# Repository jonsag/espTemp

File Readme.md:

# espTemp

An ESP-01 module with a DHT22 temperature sensor  
KiCad/espTemp/espTemp.png
Modified from [https://randomnerdtutorials.com/esp8266-dht11dht22-temperature-and-humidity-web-server-with-arduino-ide/](https://randomnerdtutorials.com/esp8266-dht11dht22-temperature-and-humidity-web-server-with-arduino-ide/)

## Hardware

Build according to schematics in KiCAD.  

## Software

Copy file wifiConfig.h.template in espTemp-PIO/src to wifiConfig.h.  
>$ cp espTemp-PIO/src/wifiConfig.h.template espTemp-PIO/src/wifiConfig.h

Edit the new file, entering your SSID and password.  
Compile and upload.  

Connect via serial (while module is still in  programmer) to find out IP and port.  

## Pins on the ESP-01

Pin         Input       Output  
5   GPIO0   pulled up   OK          connected to FLASH button, boot fails if pulled LOW  
2   GPIO1   TX pin      OK          HIGH at boot, debug output at boot, boot fails if pulled LOW  
3   GPIO2   pulled up   OK          HIGH at boot, connected to on-board LED, boot fails if pulled LOW  
7   GPIO3   OK          RX pin      HIGH at boot

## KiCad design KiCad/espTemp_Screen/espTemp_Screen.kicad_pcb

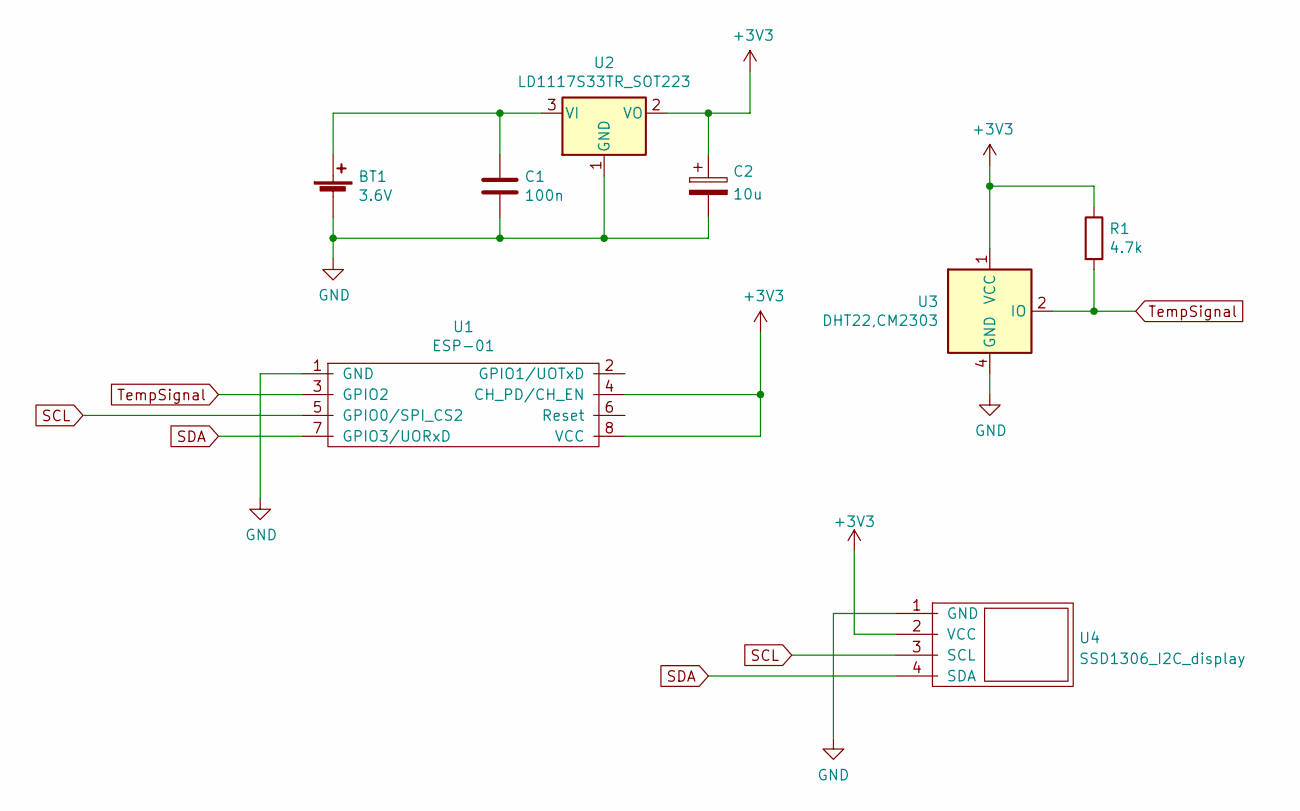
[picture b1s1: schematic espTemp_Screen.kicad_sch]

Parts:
BT1: 3.6V; 2-pin_power_input_header_larger_pads
C1: 100n; C_Disc_D3.0mm_W1.6mm_P2.50mm_larg
C2: 10u; CP_Radial_D5.0mm_P2.50mm_larger_pads
R1: 4.7k; R_Axial_DIN0207_L6.3mm_D2.5mm_P10.16mm_Horizontal_larger_pa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
U1: ESP-01; ESP-01_w_pin_socket_large
U2: LD1117S33TR_SOT223; TO-220-3_Horizontal_TabDown_large
U3: DHT22,CM2303; DHT22,RHT03,CM2303_100mil_large
U4: SSD1306_I2C_display; SSD1306_I2C_0.96_OLED_display_large

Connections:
+3V3: C2.1, R1.1, U1.4 (CH_PD/CH_EN), U1.8 (VCC), U2.2 (VO), U3.1 (VCC), U4.2 (VCC)
GND: BT1.2 (-), C1.2, C2.2, U1.1 (GND), U2.1 (GND), U3.4 (GND), U4.1 (GND)
unnamed: BT1.1 (+), C1.1, U2.3 (VI)
SCL: U1.5 (GPIO0/SPI_CS2), U4.3 (SCL)
SDA: U1.7 (GPIO3/UORxD), U4.4 (SDA)
TempSignal: R1.2, U1.3 (GPIO2), U3.2 (IO)

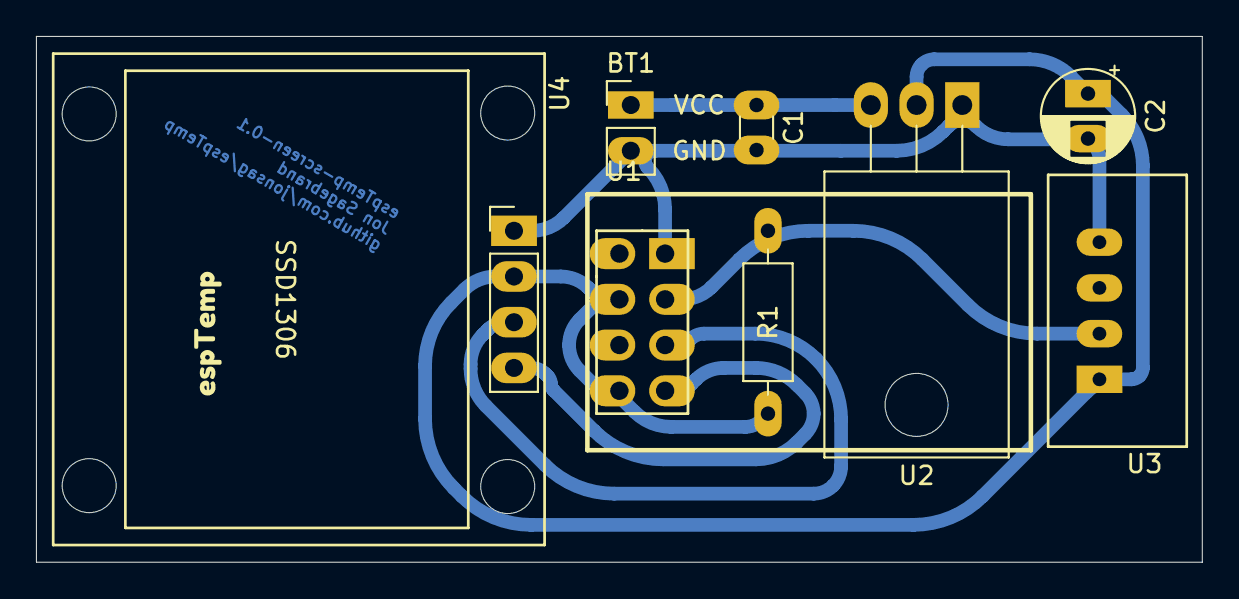
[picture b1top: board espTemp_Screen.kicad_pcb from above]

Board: 2 copper layers, 64.8 x 29.2 mm, 9 parts (0 on the bottom side), 6 nets.

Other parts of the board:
kibuzzard-62077BA3: G***; kibuzzard-62077BA3

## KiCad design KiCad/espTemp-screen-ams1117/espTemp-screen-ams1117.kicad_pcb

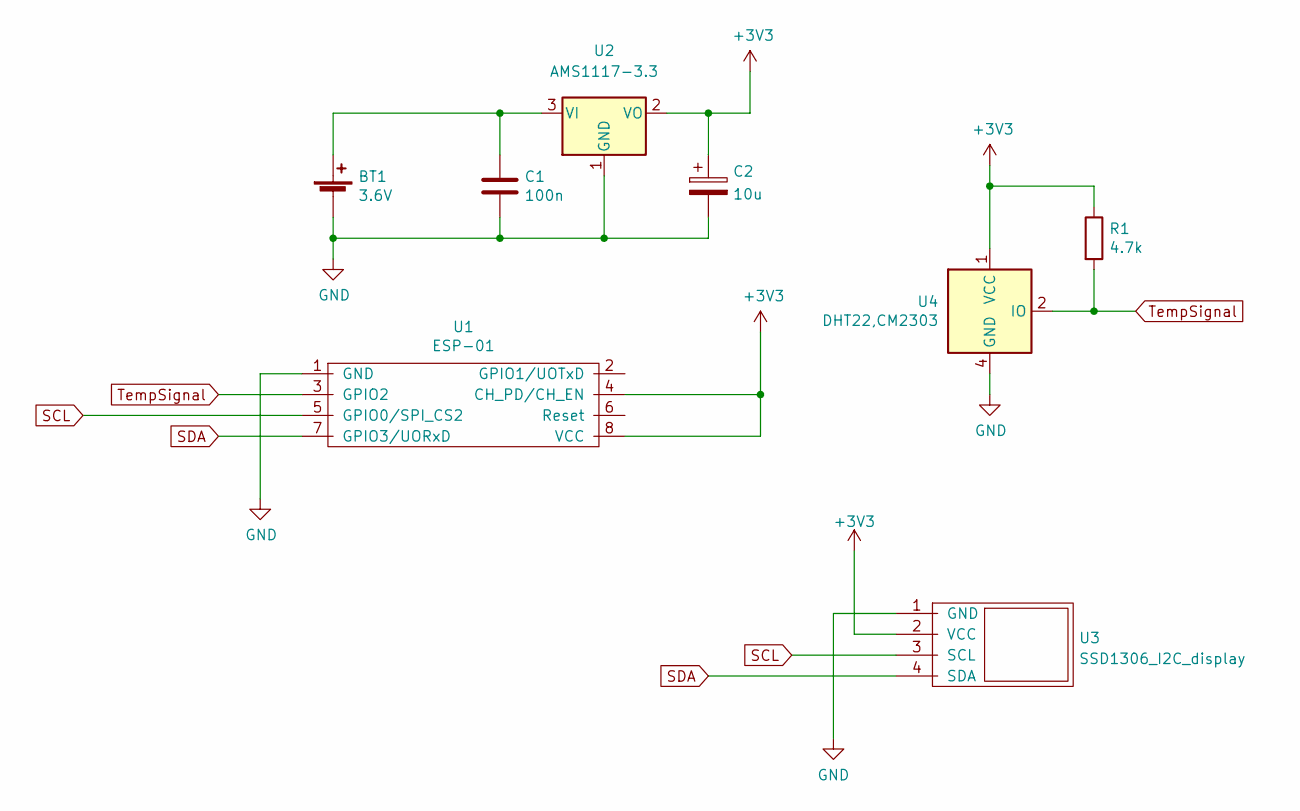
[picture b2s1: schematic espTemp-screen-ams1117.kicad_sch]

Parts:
BT1: 3.6V; 2-pin_power_input_header_larger_pads
C1: 100n; C_Disc_D3.0mm_W1.6mm_P2.50mm_larg
C2: 10u; CP_Radial_D5.0mm_P2.50mm_larger_pads
R1: 4.7k; R_Axial_DIN0207_L6.3mm_D2.5mm_P10.16mm_Horizontal_larger_pa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
U1: ESP-01; ESP-01_w_pin_socket_large
U2: AMS1117-3.3; SOT-223-3_TabPin2
U3: SSD1306_I2C_display; SSD1306_I2C_0.96_OLED_display_large
U4: DHT22,CM2303; DHT22,RHT03,CM2303_100mil_large

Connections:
+3V3: C2.1, R1.1, U1.4 (CH_PD/CH_EN), U1.8 (VCC), U2.2 (VO), U3.2 (VCC), U4.1 (VCC)
GND: BT1.2 (-), C1.2, C2.2, U1.1 (GND), U2.1 (GND), U3.1 (GND), U4.4 (GND)
unnamed: BT1.1 (+), C1.1, U2.3 (VI)
SCL: U1.5 (GPIO0/SPI_CS2), U3.3 (SCL)
SDA: U1.7 (GPIO3/UORxD), U3.4 (SDA)
TempSignal: R1.2, U1.3 (GPIO2), U4.2 (IO)

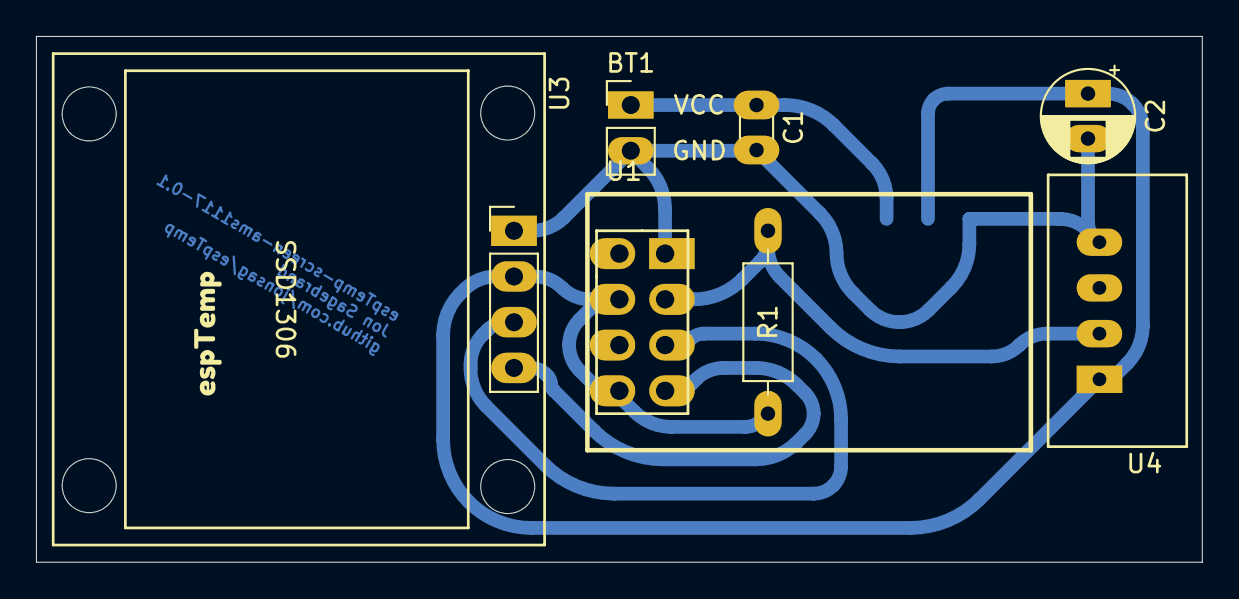
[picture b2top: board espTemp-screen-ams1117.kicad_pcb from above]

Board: 2 copper layers, 64.8 x 29.2 mm, 9 parts (1 on the bottom side), 6 nets.

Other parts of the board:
kibuzzard-62077BA3: G***; kibuzzard-62077BA3

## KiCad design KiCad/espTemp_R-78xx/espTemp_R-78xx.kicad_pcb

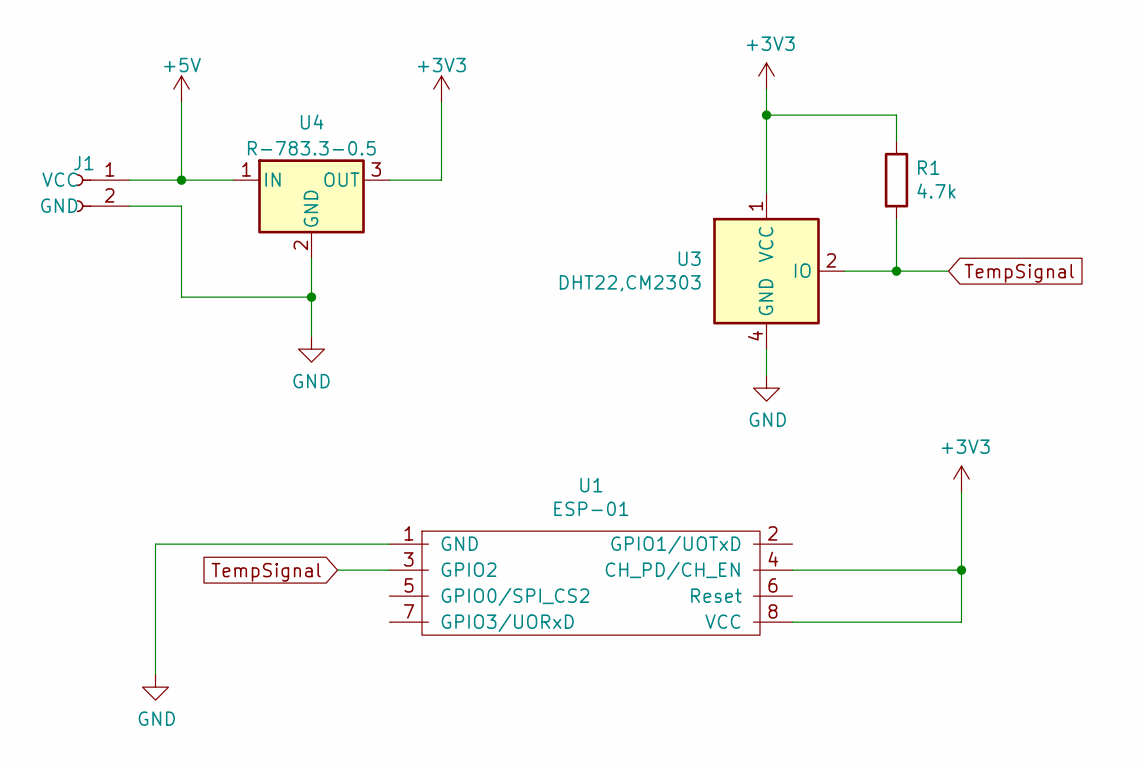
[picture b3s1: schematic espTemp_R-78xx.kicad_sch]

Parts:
J1: 2-pin_power_input_header; 2-pin Power Input Header angled large
R1: 4.7k; R_Axial_DIN0207_L6.3mm_D2.5mm_P10.16mm_Horizontal_larger_pa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
U1: ESP-01; ESP-01_w_pin_socket_large
U3: DHT22,CM2303; DHT22,RHT03,CM2303_100mil_large
U4: R-783.3-0.5; Converter_DCDC_RECOM_R-78E-0.5_THT

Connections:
+3V3: R1.1, U1.4 (CH_PD/CH_EN), U1.8 (VCC), U3.1 (VCC), U4.3 (OUT)
+5V: J1.1 (VCC), U4.1 (IN)
GND: J1.2 (GND), U1.1 (GND), U3.4 (GND), U4.2 (GND)
TempSignal: R1.2, U1.3 (GPIO2), U3.2 (IO)

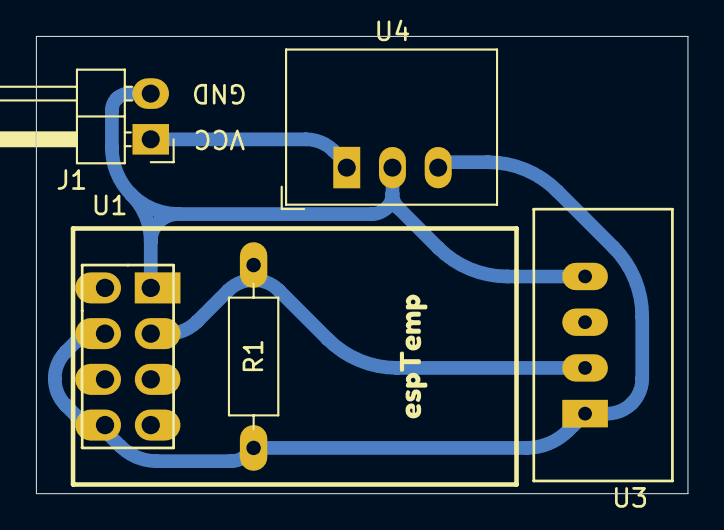
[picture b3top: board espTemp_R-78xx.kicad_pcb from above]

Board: 2 copper layers, 36.2 x 25.4 mm, 6 parts (0 on the bottom side), 4 nets.

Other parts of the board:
kibuzzard-62077BA3: G***; kibuzzard-62077BA3

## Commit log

2021-12-01 Readme and deletes
2021-12-01 PIO project
2021-12-01 change pin and sensor type
2021-12-01 readme
2021-12-13 kicad
2021-12-14 larger vias
2021-12-14 now dht22
2021-12-14 Readme and wifi config
2021-12-14 DHT22, DHT type
2021-12-15 src config
2021-12-15 100mil DHT on PCB
2021-12-26 KiCAD 6.0
2021-12-27 KiCAD 6.x
2021-12-27 fixed kicad
2021-12-27 3d view
2021-12-27 image
2022-03-21 kicad6
2022-04-23 readme and pcb
2022-04-24 other regulator solutions
2022-04-24 pcb with screen
2022-04-24 screen test
2022-12-14 images etc.
2022-12-14 more images on readme
2022-12-14 deleted .vscode
2022-12-15 new pcb, readme
2025-02-09 kicad v8
2025-02-09 workspace
2025-02-09 major rework, implementing mqtt
2025-02-09 some cleaning
2025-02-10 mqtt now works
2025-02-10 nodemcu
2025-02-11 chip id in hex
2025-02-11 added nodemcu v2
2025-02-11 git confusion
